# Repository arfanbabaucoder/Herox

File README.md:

# HeroX

HeroX is my custom full-size mechanical keyboard project, built around a **Seeed Studio XIAO nRF52840**.

so basically i wanted a full-size board that could do Bluetooth and normal USB, but i also wanted to go further than just switches on a PCB.. per-key RGB, haptics, a media knob, battery tracking, multiple Bluetooth profiles, a proper 4-layer board and a custom case. i designed the electronics in KiCad, worked on the case in Fusion 360 and put together the firmware side too, which turned into a much bigger rabbit hole than expected lol

## why i made this

i wanted a keyboard that i could actually use as a daily driver without giving up the full-size layout, numpad, navigation cluster or function row, but i didnt want it to be just another giant boring rectangle either

main goals :

- design a full-size keyboard PCB in KiCad
- support Bluetooth and wired USB-C
- scan the keyboard matrix using I2C GPIO expanders so the small XIAO controller has enough pins
- add addressable SK6812 MINI-E RGB lighting
- include a media encoder, haptic feedback and battery monitoring
- make a proper 4-layer PCB intended for manufacturing
- design a custom case in Fusion 360
- keep the project files, production references, images and BOM together so the build is reproducible

the fun part is that everything affects everything else.. a small PCB change can affect case clearances, connector access and firmware pin assignments. thats the kind of detail that makes a custom keyboard project way more involved than it looks from the top

## project status

HeroX is documented here as a design project with CAD, PCB screenshots, firmware-related screenshots and a parts list. the hardware still needs to be assembled and tested before i can claim that every feature works on a finished physical board, so treat this as a design/build project rather than a fully validated retail product

whats in this repo :

- `3D CAD/` — exported 3D model files
- `BOM Images/` — supplier and component sourcing screenshots
- `Firmware/` — firmware-related project files
- `Fusion/` — Fusion 360 design files
- `Images/` — PCB, schematic, CAD and firmware screenshots
- `PCB/` — KiCad PCB design files
- `PDFs/` — exported project documents, if present
- `Production/` — manufacturing outputs, if present
- `BOM.csv` — parts list, supplier links and estimated prices

## hardware summary

| | |
|---|---|
| Project | HeroX |
| Layout | Full-size mechanical keyboard |
| Controller | Seeed Studio XIAO nRF52840 |
| Connectivity target | Bluetooth LE and wired USB-C |
| Matrix support | I2C GPIO expanders (PCA9555-compatible parts listed in BOM) |
| Switch diodes | 1N4148W SOD-123 |
| RGB | SK6812 MINI-E addressable LEDs |
| Battery monitoring | MAX17048 fuel-gauge IC listed in BOM |
| Haptics | DRV2605L haptic-driver IC listed in BOM |
| Controls | Rotary/media encoder shown in the project design |
| Switches | Akko V3 Creamy Blue Pro 5-pin MX switches |
| Keycaps | 104/108-key ANSI PBT set |
| Stabilizers | DUROCK V3 100% PCB-mount kit |
| PCB | 4-layer board quote listed in the BOM |
| CAD | Fusion 360 and exported 3D files |

some of the interesting engineering is hidden underneath the keycaps.. the PCB has to fit the whole matrix, lighting and support circuits, while the case needs to line up with the switches, ports and controls. the CAD and PCB images below show the project from a few different angles

## images

### PCB and switch layout

### PCB routing and board layers

### schematic

the schematic screenshots show the keyboard matrix and the supporting circuits used across the design

### firmware and build screenshots

### CAD and case

## repo file checklist

the folder names in the current project are:

- `PCB/` — KiCad design files
- `3D CAD/` — 3D exports
- `Fusion/` — editable Fusion design files
- `Firmware/` — firmware files
- `Production/` — manufacturing outputs
- `PDFs/` — PDF exports
- `Images/` — project screenshots used in this README
- `BOM Images/` — sourcing screenshots
- `BOM.csv` — complete bill of materials

the exact filenames inside each folder may change as the project gets updated, so open the folders to find the latest versions. this README intentionally uses the visible folder structure rather than guessing filenames that may not exist in the repository

## cad

the case was designed in Fusion 360. the `Fusion/` folder is intended for the editable design, while `3D CAD/` contains exported geometry for viewing, modifying or preparing for printing. check the available formats in those folders before starting a print or manufacturing order

the case and PCB need to be checked together before fabrication: switch alignment, board mounting, connector access and clearance around the controls all matter. use the supplied CAD and PCB files as the source of truth for the current revision

## firmware note

the project includes a `Firmware/` folder and firmware/build screenshots. the controller listed in the BOM is the Seeed Studio XIAO nRF52840, and the design includes components associated with wireless operation, RGB, battery monitoring and haptic feedback

firmware features and flashing steps should be confirmed against the actual files in `Firmware/` before building. i dont want to claim a particular key combination, flashing image or feature is ready until it has been checked against the committed firmware revision

## bom

the full bill of materials is in [`BOM.csv`](BOM.csv). it includes the part description, quantity, supplier, supplier link and listed price in rupees. supplier prices and stock can change, and some quantities reflect supplier pack sizes or minimum order quantities rather than the exact number installed on the keyboard

**listed BOM total: ₹36,382.32**

a few notable parts from the BOM:

| Part | Purpose |
|---|---|
| Seeed Studio XIAO nRF52840 | Main controller |
| PCA9555DWR I/O expanders | Expand available GPIO for the keyboard matrix |
| 1N4148W SOD-123 diodes | Per-switch matrix diodes |
| SK6812 MINI-E | Addressable RGB lighting |
| MAX17048 fuel gauge | Battery monitoring |
| DRV2605L | Haptic driver |
| Akko V3 Creamy Blue Pro switches | Mechanical key switches |
| DUROCK V3 stabilizer kit | Stabilization for larger keys |
| 104/108-key ANSI PBT set | Keycaps |
| 4-layer PCB | Main keyboard circuit board |

prices are the values currently captured in the BOM, not a guaranteed final build cost. the total can change with shipping, taxes, revised quotes, spare parts and supplier minimums. check the links in `BOM.csv` before ordering anything

## build notes

- inspect the PCB and schematic before ordering a board
- verify the exact component substitutions and footprints against the BOM and KiCad files
- check the CAD exports against the current PCB revision before printing the case
- use a suitable protected battery and verify polarity and connector wiring before connecting it
- test the board in stages instead of powering every subsystem at once
- confirm firmware configuration and flashing instructions from the files in `Firmware/`

## contributing / questions

this is a personal custom keyboard project, and im sharing the design files and build notes so the work is easier to understand and build on. if you spot an issue or have a suggestion, feel free to open an issue on GitHub

thanks for checking out HeroX.. this project is a mix of PCB design, CAD, sourcing and embedded work, and its been a pretty great way to learn how all those pieces fit together :)

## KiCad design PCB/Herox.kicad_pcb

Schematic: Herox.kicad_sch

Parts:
A1: Seeeduino XIAO nRF52840; Xiao_nRF52840_ACH
C1: 100n U1; C_0603_1608Metric
C2: 100n U2; C_0603_1608Metric
C3: 10u BAT; C_0805_2012Metric
C4: 10u MCU; C_0805_2012Metric
C5: 47u RGB; C_0805_2012Metric
C6: 1u DRV REG; C_0603_1608Metric
C7: 100nF X7R; C_0603_1608Metric
D1, D2, D3, D4, D5, D6, D7, D8, D9, D10, D11, D12, D13, D14, D15, D16, D17, D18, D19, D20, D21, D22, D23, D24, D25, D26, D27, D28, D29, D30, D31, D32, D33, D34, D35, D36, D37, D38, D39, D40, D41, D42, D43, D44, D45, D46, D47, D48, D49, D50, D51, D52, D53, D54, D55, D56, D57, D58, D59, D60, D61, D62, D63, D64, D65, D66, D67, D68, D69, D70, D71, D72, D73, D74, D75, D76, D77, D78, D79, D80, D81, D82, D83, D84, D85, D86, D87, D88, D89, D90, D91, D92, D93, D94, D95, D96, D97, D98, D99, D100, D101, D102, D103, D104: 1N4148W; D_SOD-123
ENC1: MEDIA ENCODER; RotaryEncoder_Alps_EC11E-Switch_Vertical_H20mm
F1: PTC 1.1A; Fuse_1206_3216Metric
F2: PTC 0.5A / USB RGB; Fuse_1206_3216Metric; Manufacturer Part Number 0ZCJ0050FF2G
J1: PROTECTED Li-Po 3.7V; JST_PH_S2B-PH-K_1x02_P2.00mm_Horizontal
J2: LRA ACTUATOR; JST_PH_S2B-PH-K_1x02_P2.00mm_Horizontal
J3: LOW-POWER DISPLAY; PinHeader_1x06_P2.54mm_Vertical
J4: AMBIENT SENSOR / EXPANSION; PinHeader_1x06_P2.54mm_Vertical
J5: SWD DEBUG; PinHeader_1x04_P2.54mm_Vertical
LED1, LED2, LED3, LED4, LED5, LED6, LED7, LED8, LED9, LED10, LED11, LED12, LED13, LED14, LED15, LED16, LED17, LED18, LED19, LED20, LED21, LED22, LED23, LED24, LED25, LED26, LED27, LED28, LED29, LED30, LED31, LED32, LED33, LED34, LED35, LED36, LED37, LED38, LED39, LED40, LED41, LED42, LED43, LED44, LED45, LED46, LED47, LED48, LED49, LED50, LED51, LED52, LED53, LED54, LED55, LED56, LED57, LED58, LED59, LED60, LED61, LED62, LED63, LED64, LED65, LED66, LED67, LED68, LED69, LED70, LED71, LED72, LED73, LED74, LED75, LED76, LED77, LED78, LED79, LED80, LED81, LED82, LED83, LED84, LED85, LED86, LED87, LED88, LED89, LED90, LED91, LED92, LED93, LED94, LED95, LED96, LED97, LED98, LED99, LED100, LED101, LED102, LED103, LED104: SK6812MINI-E; LED_SK6812MINI-E_3.2x2.8mm_P1.5mm_ReverseMount
LED105, LED106: XL-1608UGC-04 GREEN; LED_0603_1608Metric
LED107, LED108, LED109: LTST-C193TBKT-5A BLUE; LED_0603_1608Metric
R1: 4.7k SDA; R_0603_1608Metric
R2: 4.7k SCL; R_0603_1608Metric
R3: 10k INT; R_0603_1608Metric
R4, R5, R6, R7, R8: 1k STATUS; R_0603_1608Metric
R12: 33R; R_0603_1608Metric
SW1: Esc; SW_MX_1.00u
SW2: F1; SW_MX_1.00u
SW3: F2; SW_MX_1.00u
SW4: F3; SW_MX_1.00u
SW5: F4; SW_MX_1.00u
SW6: F5; SW_MX_1.00u
SW7: F6; SW_MX_1.00u
SW8: F7; SW_MX_1.00u
SW9: F8; SW_MX_1.00u
SW10: F9; SW_MX_1.00u
SW11: F10; SW_MX_1.00u
SW12: F11; SW_MX_1.00u
SW13: F12; SW_MX_1.00u
SW14: PrtSc; SW_MX_1.00u
SW15: Scroll; SW_MX_1.00u
SW16: Pause; SW_MX_1.00u
SW17: `~; SW_MX_1.00u
SW18: 1!; SW_MX_1.00u
SW19: 2@; SW_MX_1.00u
SW20: 3#; SW_MX_1.00u
SW21: 4$; SW_MX_1.00u
SW22: 5%; SW_MX_1.00u
SW23: 6^; SW_MX_1.00u
SW24: 7&; SW_MX_1.00u
SW25: 8*; SW_MX_1.00u
SW26: 9(; SW_MX_1.00u
SW27: 0); SW_MX_1.00u
SW28: -_; SW_MX_1.00u
SW29: =+; SW_MX_1.00u
SW30: Backspace; SW_MX_2.00u
SW31: Insert; SW_MX_1.00u
SW32: Home; SW_MX_1.00u
SW33: PgUp; SW_MX_1.00u
SW34: Num; SW_MX_1.00u
SW35: /; SW_MX_1.00u
SW36: *; SW_MX_1.00u
SW37: -; SW_MX_1.00u
SW38: Tab; SW_MX_1.50u
SW39: Q; SW_MX_1.00u
SW40: W; SW_MX_1.00u
SW41: E; SW_MX_1.00u
SW42: R; SW_MX_1.00u
SW43: T; SW_MX_1.00u
SW44: Y; SW_MX_1.00u
SW45: U; SW_MX_1.00u
SW46: I; SW_MX_1.00u
SW47: O; SW_MX_1.00u
SW48: P; SW_MX_1.00u
SW49: [{; SW_MX_1.00u
SW50: ]}; SW_MX_1.00u
SW51: \|; SW_MX_1.50u
SW52: Delete; SW_MX_1.00u
SW53: End; SW_MX_1.00u
SW54: PgDn; SW_MX_1.00u
SW55: 7; SW_MX_1.00u
SW56: 8; SW_MX_1.00u
SW57: 9; SW_MX_1.00u
SW58: +; SW_MX_2.00u_Vertical
SW59: Caps; SW_MX_1.75u
SW60: A; SW_MX_1.00u
SW61: S; SW_MX_1.00u
SW62: D; SW_MX_1.00u
SW63: F; SW_MX_1.00u
SW64: G; SW_MX_1.00u
SW65: H; SW_MX_1.00u
SW66: J; SW_MX_1.00u
SW67: K; SW_MX_1.00u
SW68: L; SW_MX_1.00u
SW69: ;:; SW_MX_1.00u
SW70: '"; SW_MX_1.00u
SW71: Enter; SW_MX_2.25u
SW72: 4; SW_MX_1.00u
SW73: 5; SW_MX_1.00u
SW74: 6; SW_MX_1.00u
SW75: LShift; SW_MX_2.25u
SW76: Z; SW_MX_1.00u
SW77: X; SW_MX_1.00u
SW78: C; SW_MX_1.00u
SW79: V; SW_MX_1.00u
SW80: B; SW_MX_1.00u
SW81: N; SW_MX_1.00u
SW82: M; SW_MX_1.00u
SW83: ,<; SW_MX_1.00u
SW84: .>; SW_MX_1.00u
SW85: /?; SW_MX_1.00u
SW86: RShift; SW_MX_2.75u
SW87: Up; SW_MX_1.00u
SW88: 1; SW_MX_1.00u
SW89: 2; SW_MX_1.00u
SW90: 3; SW_MX_1.00u
SW91: NEnter; SW_MX_2.00u_Vertical
SW92: LCtrl; SW_MX_1.25u
SW93: LWin; SW_MX_1.25u
SW94: LAlt; SW_MX_1.25u
SW95: Space; SW_MX_6.25u
SW96: RAlt; SW_MX_1.25u
SW97: RWin; SW_MX_1.25u
SW98: Menu; SW_MX_1.25u
SW99: RCtrl; SW_MX_1.25u
SW100: Left; SW_MX_1.00u
SW101: Down; SW_MX_1.00u
SW102: Right; SW_MX_1.00u
SW103: 0; SW_MX_2.00u
SW104: .; SW_MX_1.00u
SWP1: HARD POWER; SW_SPDT_CK_JS102011SAQN
U1: TCA9555DW / ROW DRIVE; SOIC-24W_7.5x15.4mm_P1.27mm
U2: TCA9555DW / COLUMN SENSE; SOIC-24W_7.5x15.4mm_P1.27mm
U3: MAX17048G+T10 FUEL GAUGE; TDFN-8-1EP_2x2mm_P0.5mm_EP0.8x1.2mm
U4: DRV2605L HAPTIC DRIVER; MSOP-10_3x3mm_P0.5mm
U5: 74LVC1G125GW,125; SOT-353_SC-70-5; Manufacturer Part Number 74LVC1G125GW,125

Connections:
/+3V3: A1.10 (3V3), C1.1, C2.1, C4.1, J3.2, J4.2, J5.2, R1.1, R2.1, R3.1, R4.1, R5.1, R6.1, R7.1, R8.1, U1.24 (VCC), U2.21 (A0), U2.24 (VCC), U4.5 (EN), U4.6 (VDD/NC), U4.10 (VDD)
/+5V_RGB: C5.1, C7.1, F2.2, LED1.3 (VDD), LED2.3 (VDD), LED3.3 (VDD), LED4.3 (VDD), LED5.3 (VDD), LED6.3 (VDD), LED7.3 (VDD), LED8.3 (VDD), LED9.3 (VDD), LED10.3 (VDD), LED11.3 (VDD), LED12.3 (VDD), LED13.3 (VDD), LED14.3 (VDD), LED15.3 (VDD), LED16.3 (VDD), LED17.3 (VDD), LED18.3 (VDD), LED19.3 (VDD), LED20.3 (VDD), LED21.3 (VDD), LED22.3 (VDD), LED23.3 (VDD), LED24.3 (VDD), LED25.3 (VDD), LED26.3 (VDD), LED27.3 (VDD), LED28.3 (VDD), LED29.3 (VDD), LED30.3 (VDD), LED31.3 (VDD), LED32.3 (VDD), LED33.3 (VDD), LED34.3 (VDD), LED35.3 (VDD), LED36.3 (VDD), LED37.3 (VDD), LED38.3 (VDD), LED39.3 (VDD), LED40.3 (VDD), LED41.3 (VDD), LED42.3 (VDD), LED43.3 (VDD), LED44.3 (VDD), LED45.3 (VDD), LED46.3 (VDD), LED47.3 (VDD), LED48.3 (VDD), LED49.3 (VDD), LED50.3 (VDD), LED51.3 (VDD), LED52.3 (VDD), LED53.3 (VDD), LED54.3 (VDD), LED55.3 (VDD), LED56.3 (VDD), LED57.3 (VDD), LED58.3 (VDD), LED59.3 (VDD), LED60.3 (VDD), LED61.3 (VDD), LED62.3 (VDD), LED63.3 (VDD), LED64.3 (VDD), LED65.3 (VDD), LED66.3 (VDD), LED67.3 (VDD), LED68.3 (VDD), LED69.3 (VDD), LED70.3 (VDD), LED71.3 (VDD), LED72.3 (VDD), LED73.3 (VDD), LED74.3 (VDD), LED75.3 (VDD), LED76.3 (VDD), LED77.3 (VDD), LED78.3 (VDD), LED79.3 (VDD), LED80.3 (VDD), LED81.3 (VDD), LED82.3 (VDD), LED83.3 (VDD), LED84.3 (VDD), LED85.3 (VDD), LED86.3 (VDD), LED87.3 (VDD), LED88.3 (VDD), LED89.3 (VDD), LED90.3 (VDD), LED91.3 (VDD), LED92.3 (VDD), LED93.3 (VDD), LED94.3 (VDD), LED95.3 (VDD), LED96.3 (VDD), LED97.3 (VDD), LED98.3 (VDD), LED99.3 (VDD), LED100.3 (VDD), LED101.3 (VDD), LED102.3 (VDD), LED103.3 (VDD), LED104.3 (VDD), U5.5 (VCC)
/COL0: SW1.1, SW14.1, SW27.1, SW40.1, SW53.1, SW66.1, SW79.1, SW92.1, U2.4 (P00)
/COL1: SW2.1, SW15.1, SW28.1, SW41.1, SW54.1, SW67.1, SW80.1, SW93.1, U2.5 (P01)
/COL2: SW3.1, SW16.1, SW29.1, SW42.1, SW55.1, SW68.1, SW81.1, SW94.1, U2.6 (P02)
/COL3: SW4.1, SW17.1, SW30.1, SW43.1, SW56.1, SW69.1, SW82.1, SW95.1, U2.7 (P03)
/COL4: SW5.1, SW18.1, SW31.1, SW44.1, SW57.1, SW70.1, SW83.1, SW96.1, U2.8 (P04)
/COL5: SW6.1, SW19.1, SW32.1, SW45.1, SW58.1, SW71.1, SW84.1, SW97.1, U2.9 (P05)
/COL6: SW7.1, SW20.1, SW33.1, SW46.1, SW59.1, SW72.1, SW85.1, SW98.1, U2.10 (P06)
/COL7: SW8.1, SW21.1, SW34.1, SW47.1, SW60.1, SW73.1, SW86.1, SW99.1, U2.11 (P07)
/COL8: SW9.1, SW22.1, SW35.1, SW48.1, SW61.1, SW74.1, SW87.1, SW100.1, U2.13 (P10)
/COL9: SW10.1, SW23.1, SW36.1, SW49.1, SW62.1, SW75.1, SW88.1, SW101.1, U2.14 (P11)
/COL10: SW11.1, SW24.1, SW37.1, SW50.1, SW63.1, SW76.1, SW89.1, SW102.1, U2.15 (P12)
/COL11: SW12.1, SW25.1, SW38.1, SW51.1, SW64.1, SW77.1, SW90.1, SW103.1, U2.16 (P13)
/COL12: SW13.1, SW26.1, SW39.1, SW52.1, SW65.1, SW78.1, SW91.1, SW104.1, U2.17 (P14)
/DISP_INT: A1.11 (P1.15), J3.5
/DRV_REG: C6.1, U4.1 (REG)
/ENC_A: A1.3 (P0.28), ENC1.A
/ENC_B: A1.4 (P0.29), ENC1.C
/ENC_SW: A1.7 (P1.11), ENC1.S1
/EX_INT: A1.2 (P0.03), J4.5, R3.2, U1.1 (~INT), U2.1 (~INT)
/FUEL_INT: A1.12 (P1.14), U3.5
/GND: A1.9 (GND), A1.15 (BAT-), A1.22 (GND), C1.2, C2.2, C3.2, C4.2, C5.2, C6.2, C7.2, ENC1.B, ENC1.S2, J1.2, J3.1, J4.1, J5.1, LED1.1 (VSS), LED2.1 (VSS), LED3.1 (VSS), LED4.1 (VSS), LED5.1 (VSS), LED6.1 (VSS), LED7.1 (VSS), LED8.1 (VSS), LED9.1 (VSS), LED10.1 (VSS), LED11.1 (VSS), LED12.1 (VSS), LED13.1 (VSS), LED14.1 (VSS), LED15.1 (VSS), LED16.1 (VSS), LED17.1 (VSS), LED18.1 (VSS), LED19.1 (VSS), LED20.1 (VSS), LED21.1 (VSS), LED22.1 (VSS), LED23.1 (VSS), LED24.1 (VSS), LED25.1 (VSS), LED26.1 (VSS), LED27.1 (VSS), LED28.1 (VSS), LED29.1 (VSS), LED30.1 (VSS), LED31.1 (VSS), LED32.1 (VSS), LED33.1 (VSS), LED34.1 (VSS), LED35.1 (VSS), LED36.1 (VSS), LED37.1 (VSS), LED38.1 (VSS), LED39.1 (VSS), LED40.1 (VSS), LED41.1 (VSS), LED42.1 (VSS), LED43.1 (VSS), LED44.1 (VSS), LED45.1 (VSS), LED46.1 (VSS), LED47.1 (VSS), LED48.1 (VSS), LED49.1 (VSS), LED50.1 (VSS), LED51.1 (VSS), LED52.1 (VSS), LED53.1 (VSS), LED54.1 (VSS), LED55.1 (VSS), LED56.1 (VSS), LED57.1 (VSS), LED58.1 (VSS), LED59.1 (VSS), LED60.1 (VSS), LED61.1 (VSS), LED62.1 (VSS), LED63.1 (VSS), LED64.1 (VSS), LED65.1 (VSS), LED66.1 (VSS), LED67.1 (VSS), LED68.1 (VSS), LED69.1 (VSS), LED70.1 (VSS), LED71.1 (VSS), LED72.1 (VSS), LED73.1 (VSS), LED74.1 (VSS), LED75.1 (VSS), LED76.1 (VSS), LED77.1 (VSS), LED78.1 (VSS), LED79.1 (VSS), LED80.1 (VSS), LED81.1 (VSS), LED82.1 (VSS), LED83.1 (VSS), LED84.1 (VSS), LED85.1 (VSS), LED86.1 (VSS), LED87.1 (VSS), LED88.1 (VSS), LED89.1 (VSS), LED90.1 (VSS), LED91.1 (VSS), LED92.1 (VSS), LED93.1 (VSS), LED94.1 (VSS), LED95.1 (VSS), LED96.1 (VSS), LED97.1 (VSS), LED98.1 (VSS), LED99.1 (VSS), LED100.1 (VSS), LED101.1 (VSS), LED102.1 (VSS), LED103.1 (VSS), LED104.1 (VSS), U1.2 (A1), U1.3 (A2), U1.12 (GND), U1.21 (A0), U2.2 (A1), U2.3 (A2), U2.12 (GND), U3.3, U3.4, U3.9, U4.4 (IN/TRIG), U4.8 (GND), U5.1, U5.3 (GND)
/HAPTIC_N: J2.2, U4.9 (OUT-)
/HAPTIC_P: J2.1, U4.7 (OUT+)
/I2C_SCL: A1.6 (P0.05), J3.4, J4.4, R2.2, U1.22 (SCL), U2.22 (SCL), U3.7, U4.2 (SCL)
/I2C_SDA: A1.5 (P0.04), J3.3, J4.3, J5.3, R1.2, U1.23 (SDA), U2.23 (SDA), U3.6, U4.3 (SDA)
/IND_BLE1_N: LED107.1 (K), U1.15 (P12)
/IND_BLE2_N: LED108.1 (K), U1.16 (P13)
/IND_BLE3_N: LED109.1 (K), U1.17 (P14)
/IND_CAPS_N: LED105.1 (K), U1.13 (P10)
/IND_NUM_N: LED106.1 (K), U1.14 (P11)
/KSW1: D1.2 (A), SW1.2
/KSW2: D2.2 (A), SW2.2
/KSW3: D3.2 (A), SW3.2
/KSW4: D4.2 (A), SW4.2
/KSW5: D5.2 (A), SW5.2
/KSW6: D6.2 (A), SW6.2
/KSW7: D7.2 (A), SW7.2
/KSW8: D8.2 (A), SW8.2
/KSW9: D9.2 (A), SW9.2
/KSW10: D10.2 (A), SW10.2
/KSW11: D11.2 (A), SW11.2
/KSW12: D12.2 (A), SW12.2
/KSW13: D13.2 (A), SW13.2
/KSW14: D14.2 (A), SW14.2
/KSW15: D15.2 (A), SW15.2
/KSW16: D16.2 (A), SW16.2
/KSW17: D17.2 (A), SW17.2
/KSW18: D18.2 (A), SW18.2
/KSW19: D19.2 (A), SW19.2
/KSW20: D20.2 (A), SW20.2
/KSW21: D21.2 (A), SW21.2
/KSW22: D22.2 (A), SW22.2
/KSW23: D23.2 (A), SW23.2
/KSW24: D24.2 (A), SW24.2
/KSW25: D25.2 (A), SW25.2
/KSW26: D26.2 (A), SW26.2
/KSW27: D27.2 (A), SW27.2
/KSW28: D28.2 (A), SW28.2
/KSW29: D29.2 (A), SW29.2
/KSW30: D30.2 (A), SW30.2
/KSW31: D31.2 (A), SW31.2
/KSW32: D32.2 (A), SW32.2
/KSW33: D33.2 (A), SW33.2
/KSW34: D34.2 (A), SW34.2
/KSW35: D35.2 (A), SW35.2
/KSW36: D36.2 (A), SW36.2
/KSW37: D37.2 (A), SW37.2
/KSW38: D38.2 (A), SW38.2
/KSW39: D39.2 (A), SW39.2
/KSW40: D40.2 (A), SW40.2
/KSW41: D41.2 (A), SW41.2
/KSW42: D42.2 (A), SW42.2
/KSW43: D43.2 (A), SW43.2
/KSW44: D44.2 (A), SW44.2
/KSW45: D45.2 (A), SW45.2
/KSW46: D46.2 (A), SW46.2
/KSW47: D47.2 (A), SW47.2
/KSW48: D48.2 (A), SW48.2
/KSW49: D49.2 (A), SW49.2
/KSW50: D50.2 (A), SW50.2
/KSW51: D51.2 (A), SW51.2
/KSW52: D52.2 (A), SW52.2
/KSW53: D53.2 (A), SW53.2
/KSW54: D54.2 (A), SW54.2
/KSW55: D55.2 (A), SW55.2
/KSW56: D56.2 (A), SW56.2
/KSW57: D57.2 (A), SW57.2
/KSW58: D58.2 (A), SW58.2
/KSW59: D59.2 (A), SW59.2
/KSW60: D60.2 (A), SW60.2
/KSW61: D61.2 (A), SW61.2
/KSW62: D62.2 (A), SW62.2
/KSW63: D63.2 (A), SW63.2
/KSW64: D64.2 (A), SW64.2
/KSW65: D65.2 (A), SW65.2
/KSW66: D66.2 (A), SW66.2
/KSW67: D67.2 (A), SW67.2
/KSW68: D68.2 (A), SW68.2
/KSW69: D69.2 (A), SW69.2
/KSW70: D70.2 (A), SW70.2
/KSW71: D71.2 (A), SW71.2
/KSW72: D72.2 (A), SW72.2
/KSW73: D73.2 (A), SW73.2
/KSW74: D74.2 (A), SW74.2
/KSW75: D75.2 (A), SW75.2
/KSW76: D76.2 (A), SW76.2
/KSW77: D77.2 (A), SW77.2
/KSW78: D78.2 (A), SW78.2
/KSW79: D79.2 (A), SW79.2
/KSW80: D80.2 (A), SW80.2
/KSW81: D81.2 (A), SW81.2
/KSW82: D82.2 (A), SW82.2
/KSW83: D83.2 (A), SW83.2
/KSW84: D84.2 (A), SW84.2
/KSW85: D85.2 (A), SW85.2
/KSW86: D86.2 (A), SW86.2
/KSW87: D87.2 (A), SW87.2
/KSW88: D88.2 (A), SW88.2
/KSW89: D89.2 (A), SW89.2
/KSW90: D90.2 (A), SW90.2
/KSW91: D91.2 (A), SW91.2
/KSW92: D92.2 (A), SW92.2
/KSW93: D93.2 (A), SW93.2
/KSW94: D94.2 (A), SW94.2
/KSW95: D95.2 (A), SW95.2
/KSW96: D96.2 (A), SW96.2
/KSW97: D97.2 (A), SW97.2
/KSW98: D98.2 (A), SW98.2
/KSW99: D99.2 (A), SW99.2
/KSW100: D100.2 (A), SW100.2
/KSW101: D101.2 (A), SW101.2
/KSW102: D102.2 (A), SW102.2
/KSW103: D103.2 (A), SW103.2
/KSW104: D104.2 (A), SW104.2
/NRST: A1.21 (RST), J3.6, J5.4
/RGB_1: LED1.4 (DOUT), LED2.2 (DIN)
/RGB_2: LED2.4 (DOUT), LED3.2 (DIN)
/RGB_3: LED3.4 (DOUT), LED4.2 (DIN)
/RGB_4: LED4.4 (DOUT), LED5.2 (DIN)
/RGB_5: LED5.4 (DOUT), LED6.2 (DIN)
/RGB_6: LED6.4 (DOUT), LED7.2 (DIN)
/RGB_7: LED7.4 (DOUT), LED8.2 (DIN)
/RGB_8: LED8.4 (DOUT), LED9.2 (DIN)
/RGB_9: LED9.4 (DOUT), LED10.2 (DIN)
/RGB_10: LED10.4 (DOUT), LED11.2 (DIN)
/RGB_11: LED11.4 (DOUT), LED12.2 (DIN)
/RGB_12: LED12.4 (DOUT), LED13.2 (DIN)
/RGB_13: LED13.4 (DOUT), LED14.2 (DIN)
/RGB_14: LED14.4 (DOUT), LED15.2 (DIN)
/RGB_15: LED15.4 (DOUT), LED16.2 (DIN)
/RGB_16: LED16.4 (DOUT), LED17.2 (DIN)
/RGB_17: LED17.4 (DOUT), LED18.2 (DIN)
/RGB_18: LED18.4 (DOUT), LED19.2 (DIN)
/RGB_19: LED19.4 (DOUT), LED20.2 (DIN)
/RGB_20: LED20.4 (DOUT), LED21.2 (DIN)
/RGB_21: LED21.4 (DOUT), LED22.2 (DIN)
/RGB_22: LED22.4 (DOUT), LED23.2 (DIN)
/RGB_23: LED23.4 (DOUT), LED24.2 (DIN)
/RGB_24: LED24.4 (DOUT), LED25.2 (DIN)
/RGB_25: LED25.4 (DOUT), LED26.2 (DIN)
/RGB_26: LED26.4 (DOUT), LED27.2 (DIN)
/RGB_27: LED27.4 (DOUT), LED28.2 (DIN)
/RGB_28: LED28.4 (DOUT), LED29.2 (DIN)
/RGB_29: LED29.4 (DOUT), LED30.2 (DIN)
/RGB_30: LED30.4 (DOUT), LED31.2 (DIN)
/RGB_31: LED31.4 (DOUT), LED32.2 (DIN)
/RGB_32: LED32.4 (DOUT), LED33.2 (DIN)
/RGB_33: LED33.4 (DOUT), LED34.2 (DIN)
/RGB_34: LED34.4 (DOUT), LED35.2 (DIN)
/RGB_35: LED35.4 (DOUT), LED36.2 (DIN)
/RGB_36: LED36.4 (DOUT), LED37.2 (DIN)
/RGB_37: LED37.4 (DOUT), LED38.2 (DIN)
/RGB_38: LED38.4 (DOUT), LED39.2 (DIN)
/RGB_39: LED39.4 (DOUT), LED40.2 (DIN)
/RGB_40: LED40.4 (DOUT), LED41.2 (DIN)
/RGB_41: LED41.4 (DOUT), LED42.2 (DIN)
/RGB_42: LED42.4 (DOUT), LED43.2 (DIN)
/RGB_43: LED43.4 (DOUT), LED44.2 (DIN)
/RGB_44: LED44.4 (DOUT), LED45.2 (DIN)
/RGB_45: LED45.4 (DOUT), LED46.2 (DIN)
/RGB_46: LED46.4 (DOUT), LED47.2 (DIN)
/RGB_47: LED47.4 (DOUT), LED48.2 (DIN)
/RGB_48: LED48.4 (DOUT), LED49.2 (DIN)
/RGB_49: LED49.4 (DOUT), LED50.2 (DIN)
/RGB_50: LED50.4 (DOUT), LED51.2 (DIN)
/RGB_51: LED51.4 (DOUT), LED52.2 (DIN)
/RGB_52: LED52.4 (DOUT), LED53.2 (DIN)
/RGB_53: LED53.4 (DOUT), LED54.2 (DIN)
/RGB_54: LED54.4 (DOUT), LED55.2 (DIN)
/RGB_55: LED55.4 (DOUT), LED56.2 (DIN)
/RGB_56: LED56.4 (DOUT), LED57.2 (DIN)
/RGB_57: LED57.4 (DOUT), LED58.2 (DIN)
/RGB_58: LED58.4 (DOUT), LED59.2 (DIN)
/RGB_59: LED59.4 (DOUT), LED60.2 (DIN)
/RGB_60: LED60.4 (DOUT), LED61.2 (DIN)
/RGB_61: LED61.4 (DOUT), LED62.2 (DIN)
/RGB_62: LED62.4 (DOUT), LED63.2 (DIN)
/RGB_63: LED63.4 (DOUT), LED64.2 (DIN)
/RGB_64: LED64.4 (DOUT), LED65.2 (DIN)
/RGB_65: LED65.4 (DOUT), LED66.2 (DIN)
/RGB_66: LED66.4 (DOUT), LED67.2 (DIN)
/RGB_67: LED67.4 (DOUT), LED68.2 (DIN)
/RGB_68: LED68.4 (DOUT), LED69.2 (DIN)
/RGB_69: LED69.4 (DOUT), LED70.2 (DIN)
/RGB_70: LED70.4 (DOUT), LED71.2 (DIN)
/RGB_71: LED71.4 (DOUT), LED72.2 (DIN)
/RGB_72: LED72.4 (DOUT), LED73.2 (DIN)
/RGB_73: LED73.4 (DOUT), LED74.2 (DIN)
/RGB_74: LED74.4 (DOUT), LED75.2 (DIN)
/RGB_75: LED75.4 (DOUT), LED76.2 (DIN)
/RGB_76: LED76.4 (DOUT), LED77.2 (DIN)
/RGB_77: LED77.4 (DOUT), LED78.2 (DIN)
/RGB_78: LED78.4 (DOUT), LED79.2 (DIN)
/RGB_79: LED79.4 (DOUT), LED80.2 (DIN)
/RGB_80: LED80.4 (DOUT), LED81.2 (DIN)
/RGB_81: LED81.4 (DOUT), LED82.2 (DIN)
/RGB_82: LED82.4 (DOUT), LED83.2 (DIN)
/RGB_83: LED83.4 (DOUT), LED84.2 (DIN)
/RGB_84: LED84.4 (DOUT), LED85.2 (DIN)
/RGB_85: LED85.4 (DOUT), LED86.2 (DIN)
/RGB_86: LED86.4 (DOUT), LED87.2 (DIN)
/RGB_87: LED87.4 (DOUT), LED88.2 (DIN)
/RGB_88: LED88.4 (DOUT), LED89.2 (DIN)
/RGB_89: LED89.4 (DOUT), LED90.2 (DIN)
/RGB_90: LED90.4 (DOUT), LED91.2 (DIN)
/RGB_91: LED91.4 (DOUT), LED92.2 (DIN)
/RGB_92: LED92.4 (DOUT), LED93.2 (DIN)
/RGB_93: LED93.4 (DOUT), LED94.2 (DIN)
/RGB_94: LED94.4 (DOUT), LED95.2 (DIN)
/RGB_95: LED95.4 (DOUT), LED96.2 (DIN)
/RGB_96: LED96.4 (DOUT), LED97.2 (DIN)
/RGB_97: LED97.4 (DOUT), LED98.2 (DIN)
/RGB_98: LED98.4 (DOUT), LED99.2 (DIN)
/RGB_99: LED99.4 (DOUT), LED100.2 (DIN)
/RGB_100: LED100.4 (DOUT), LED101.2 (DIN)
/RGB_101: LED101.4 (DOUT), LED102.2 (DIN)
/RGB_102: LED102.4 (DOUT), LED103.2 (DIN)
/RGB_103: LED103.4 (DOUT), LED104.2 (DIN)
/RGB_DATA: LED1.2 (DIN), R12.2
/RGB_DATA_3V3: A1.1 (P0.02), U5.2
/ROW0: D1.1 (K), D2.1 (K), D3.1 (K), D4.1 (K), D5.1 (K), D6.1 (K), D7.1 (K), D8.1 (K), D9.1 (K), D10.1 (K), D11.1 (K), D12.1 (K), D13.1 (K), U1.4 (P00)
/ROW1: D14.1 (K), D15.1 (K), D16.1 (K), D17.1 (K), D18.1 (K), D19.1 (K), D20.1 (K), D21.1 (K), D22.1 (K), D23.1 (K), D24.1 (K), D25.1 (K), D26.1 (K), U1.5 (P01)
/ROW2: D27.1 (K), D28.1 (K), D29.1 (K), D30.1 (K), D31.1 (K), D32.1 (K), D33.1 (K), D34.1 (K), D35.1 (K), D36.1 (K), D37.1 (K), D38.1 (K), D39.1 (K), U1.6 (P02)
/ROW3: D40.1 (K), D41.1 (K), D42.1 (K), D43.1 (K), D44.1 (K), D45.1 (K), D46.1 (K), D47.1 (K), D48.1 (K), D49.1 (K), D50.1 (K), D51.1 (K), D52.1 (K), U1.7 (P03)
/ROW4: D53.1 (K), D54.1 (K), D55.1 (K), D56.1 (K), D57.1 (K), D58.1 (K), D59.1 (K), D60.1 (K), D61.1 (K), D62.1 (K), D63.1 (K), D64.1 (K), D65.1 (K), U1.8 (P04)
/ROW5: D66.1 (K), D67.1 (K), D68.1 (K), D69.1 (K), D70.1 (K), D71.1 (K), D72.1 (K), D73.1 (K), D74.1 (K), D75.1 (K), D76.1 (K), D77.1 (K), D78.1 (K), U1.9 (P05)
/ROW6: D79.1 (K), D80.1 (K), D81.1 (K), D82.1 (K), D83.1 (K), D84.1 (K), D85.1 (K), D86.1 (K), D87.1 (K), D88.1 (K), D89.1 (K), D90.1 (K), D91.1 (K), U1.10 (P06)
/ROW7: D92.1 (K), D93.1 (K), D94.1 (K), D95.1 (K), D96.1 (K), D97.1 (K), D98.1 (K), D99.1 (K), D100.1 (K), D101.1 (K), D102.1 (K), D103.1 (K), D104.1 (K), U1.11 (P07)
/USB_VBUS_5V: A1.8 (5V), F2.1
/VBAT_FUSED: F1.2, SWP1.1 (A)
/VBAT_RAW: F1.1, J1.1
/VBAT_SW: A1.16 (BAT+), C3.1, J4.6, SWP1.2 (B), U3.2, U3.8
unnamed: LED105.2 (A), R4.2
unnamed: LED106.2 (A), R5.2
unnamed: LED107.2 (A), R6.2
unnamed: LED108.2 (A), R7.2
unnamed: LED109.2 (A), R8.2
unnamed: R12.1, U5.4

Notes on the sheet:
ROW0
COL8
+5V_RGB
COL7
CAPS LOCK
COL1
NUM LOCK
BLE HOST 2
GND
COL2
COL10
COL5
COL9
ROW6
ROW1
BLE HOST 3
COL12
COL3
ROW2
ROW3
ROW4
COL6
BLE HOST 1
COL11
ROW5
COL0
COL4
ROW7

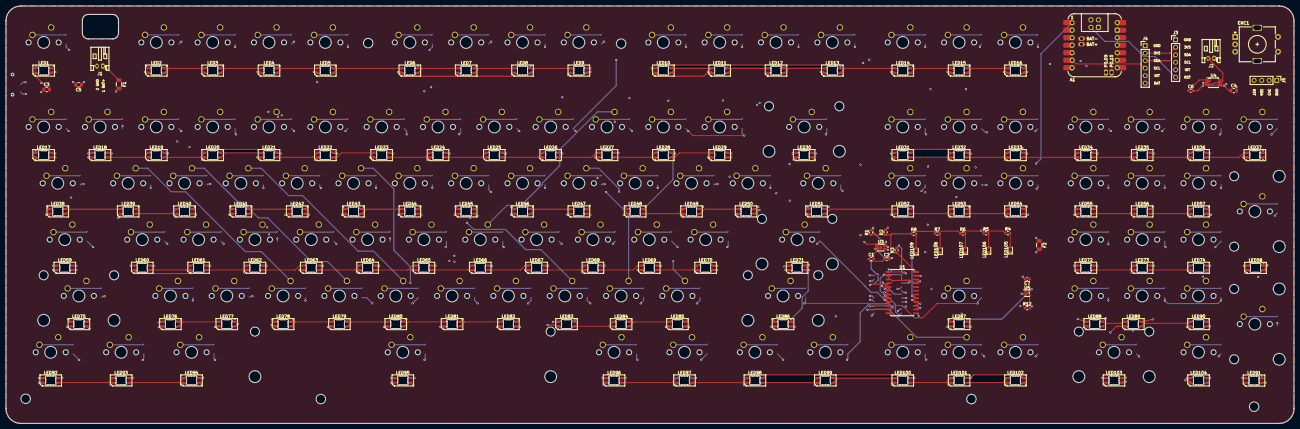
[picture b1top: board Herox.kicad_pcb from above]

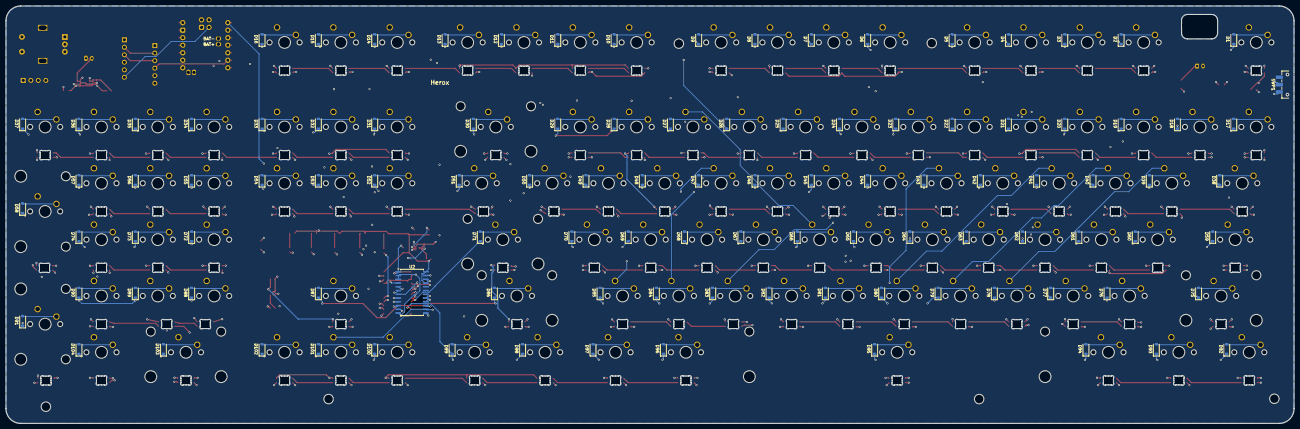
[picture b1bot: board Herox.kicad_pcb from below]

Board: 4 copper layers, 435.6 x 141.2 mm, 354 parts (106 on the bottom side), 260 nets.

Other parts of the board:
H2, H3, H5, H6, H7, H8: M3; MountingHole_3.2mm_M3

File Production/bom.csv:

Designator,Footprint,Quantity,Value,LCSC Part #
A1,Xiao_nRF52840_ACH,1,Seeeduino XIAO nRF52840,
C1,0603,1,100n U1,
C2,0603,1,100n U2,
C3,0805,1,10u BAT,
C4,0805,1,10u MCU,
C5,0805,1,47u RGB,
C6,0603,1,1u DRV REG,
C7,0603,1,100nF X7R,
"D1, D10, D100, D101, D102, D103, D104, D11, D12, D13, D14, D15, D16, D17, D18, D19, D2, D20, D21, D22, D23, D24, D25, D26, D27, D28, D29, D3, D30, D31, D32, D33, D34, D35, D36, D37, D38, D39, D4, D40, D41, D42, D43, D44, D45, D46, D47, D48, D49, D5, D50, D51, D52, D53, D54, D55, D56, D57, D58, D59, D6, D60, D61, D62, D63, D64, D65, D66, D67, D68, D69, D7, D70, D71, D72, D73, D74, D75, D76, D77, D78, D79, D8, D80, D81, D82, D83, D84, D85, D86, D87, D88, D89, D9, D90, D91, D92, D93, D94, D95, D96, D97, D98, D99",D_SOD-123,104,1N4148W,
ENC1,RotaryEncoder_Alps_EC11E-Switch_Vertical_H20mm,1,MEDIA ENCODER,
F1,1206,1,PTC 1.1A,
F2,1206,1,PTC 0.5A / USB RGB,
J1,JST_PH_S2B-PH-K_1x02_P2.00mm_Horizontal,1,PROTECTED Li-Po 3.7V,
J2,JST_PH_S2B-PH-K_1x02_P2.00mm_Horizontal,1,LRA ACTUATOR,
J3,PinHeader_1x06_P2.54mm_Vertical,1,LOW-POWER DISPLAY,
J4,PinHeader_1x06_P2.54mm_Vertical,1,AMBIENT SENSOR / EXPANSION,
J5,PinHeader_1x04_P2.54mm_Vertical,1,SWD DEBUG,
"LED1, LED10, LED100, LED101, LED102, LED103, LED104, LED11, LED12, LED13, LED14, LED15, LED16, LED17, LED18, LED19, LED2, LED20, LED21, LED22, LED23, LED24, LED25, LED26, LED27, LED28, LED29, LED3, LED30, LED31, LED32, LED33, LED34, LED35, LED36, LED37, LED38, LED39, LED4, LED40, LED41, LED42, LED43, LED44, LED45, LED46, LED47, LED48, LED49, LED5, LED50, LED51, LED52, LED53, LED54, LED55, LED56, LED57, LED58, LED59, LED6, LED60, LED61, LED62, LED63, LED64, LED65, LED66, LED67, LED68, LED69, LED7, LED70, LED71, LED72, LED73, LED74, LED75, LED76, LED77, LED78, LED79, LED8, LED80, LED81, LED82, LED83, LED84, LED85, LED86, LED87, LED88, LED89, LED9, LED90, LED91, LED92, LED93, LED94, LED95, LED96, LED97, LED98, LED99",LED_SK6812MINI-E_3.2x2.8mm_P1.5mm_ReverseMount,104,SK6812MINI-E,
"LED105, LED106",0603,2,XL-1608UGC-04 GREEN,
"LED107, LED108, LED109",0603,3,LTST-C193TBKT-5A BLUE,
R1,0603,1,4.7k SDA,
R12,0603,1,33R,
R2,0603,1,4.7k SCL,
R3,0603,1,10k INT,
"R4, R5, R6, R7, R8",0603,5,1k STATUS,
SW1,SW_MX_1.00u,1,Esc,
SW10,SW_MX_1.00u,1,F9,
SW100,SW_MX_1.00u,1,Left,
SW101,SW_MX_1.00u,1,Down,
SW102,SW_MX_1.00u,1,Right,
SW103,SW_MX_2.00u,1,0,
SW104,SW_MX_1.00u,1,.,
SW11,SW_MX_1.00u,1,F10,
SW12,SW_MX_1.00u,1,F11,
SW13,SW_MX_1.00u,1,F12,
SW14,SW_MX_1.00u,1,PrtSc,
SW15,SW_MX_1.00u,1,Scroll,
SW16,SW_MX_1.00u,1,Pause,
SW17,SW_MX_1.00u,1,`~,
SW18,SW_MX_1.00u,1,1!,
SW19,SW_MX_1.00u,1,2@,
SW2,SW_MX_1.00u,1,F1,
SW20,SW_MX_1.00u,1,3#,
SW21,SW_MX_1.00u,1,4$,
SW22,SW_MX_1.00u,1,5%,
SW23,SW_MX_1.00u,1,6^,
SW24,SW_MX_1.00u,1,7&,
SW25,SW_MX_1.00u,1,8*,
SW26,SW_MX_1.00u,1,9(,
SW27,SW_MX_1.00u,1,0),
SW28,SW_MX_1.00u,1,-_,
SW29,SW_MX_1.00u,1,=+,
SW3,SW_MX_1.00u,1,F2,
SW30,SW_MX_2.00u,1,Backspace,
SW31,SW_MX_1.00u,1,Insert,
SW32,SW_MX_1.00u,1,Home,
SW33,SW_MX_1.00u,1,PgUp,
SW34,SW_MX_1.00u,1,Num,
SW35,SW_MX_1.00u,1,/,
SW36,SW_MX_1.00u,1,*,
SW37,SW_MX_1.00u,1,-,
SW38,SW_MX_1.50u,1,Tab,
SW39,SW_MX_1.00u,1,Q,
SW4,SW_MX_1.00u,1,F3,
SW40,SW_MX_1.00u,1,W,
SW41,SW_MX_1.00u,1,E,
SW42,SW_MX_1.00u,1,R,
SW43,SW_MX_1.00u,1,T,
SW44,SW_MX_1.00u,1,Y,
SW45,SW_MX_1.00u,1,U,
SW46,SW_MX_1.00u,1,I,
SW47,SW_MX_1.00u,1,O,
SW48,SW_MX_1.00u,1,P,
SW49,SW_MX_1.00u,1,[{,
SW5,SW_MX_1.00u,1,F4,
SW50,SW_MX_1.00u,1,]},
SW51,SW_MX_1.50u,1,\|,
SW52,SW_MX_1.00u,1,Delete,
SW53,SW_MX_1.00u,1,End,
SW54,SW_MX_1.00u,1,PgDn,
SW55,SW_MX_1.00u,1,7,
SW56,SW_MX_1.00u,1,8,
SW57,SW_MX_1.00u,1,9,
SW58,SW_MX_2.00u_Vertical,1,+,
SW59,SW_MX_1.75u,1,Caps,
SW6,SW_MX_1.00u,1,F5,
SW60,SW_MX_1.00u,1,A,
SW61,SW_MX_1.00u,1,S,
SW62,SW_MX_1.00u,1,D,
SW63,SW_MX_1.00u,1,F,
SW64,SW_MX_1.00u,1,G,
SW65,SW_MX_1.00u,1,H,
SW66,SW_MX_1.00u,1,J,
SW67,SW_MX_1.00u,1,K,
SW68,SW_MX_1.00u,1,L,
SW69,SW_MX_1.00u,1,;:,
SW7,SW_MX_1.00u,1,F6,
SW70,SW_MX_1.00u,1,"'""",
SW71,SW_MX_2.25u,1,Enter,
SW72,SW_MX_1.00u,1,4,
SW73,SW_MX_1.00u,1,5,
SW74,SW_MX_1.00u,1,6,
SW75,SW_MX_2.25u,1,LShift,
SW76,SW_MX_1.00u,1,Z,
SW77,SW_MX_1.00u,1,X,
SW78,SW_MX_1.00u,1,C,
SW79,SW_MX_1.00u,1,V,
SW8,SW_MX_1.00u,1,F7,
SW80,SW_MX_1.00u,1,B,
SW81,SW_MX_1.00u,1,N,
SW82,SW_MX_1.00u,1,M,
SW83,SW_MX_1.00u,1,",<",
SW84,SW_MX_1.00u,1,.>,
SW85,SW_MX_1.00u,1,/?,
SW86,SW_MX_2.75u,1,RShift,
SW87,SW_MX_1.00u,1,Up,
SW88,SW_MX_1.00u,1,1,
SW89,SW_MX_1.00u,1,2,
SW9,SW_MX_1.00u,1,F8,
SW90,SW_MX_1.00u,1,3,
SW91,SW_MX_2.00u_Vertical,1,NEnter,
SW92,SW_MX_1.25u,1,LCtrl,
SW93,SW_MX_1.25u,1,LWin,
SW94,SW_MX_1.25u,1,LAlt,
SW95,SW_MX_6.25u,1,Space,
SW96,SW_MX_1.25u,1,RAlt,
SW97,SW_MX_1.25u,1,RWin,
SW98,SW_MX_1.25u,1,Menu,
SW99,SW_MX_1.25u,1,RCtrl,
SWP1,SW_SPDT_CK_JS102011SAQN,1,HARD POWER,
U1,SOIC-24W_7.5x15.4mm_P1.27mm,1,TCA9555DW / ROW DRIVE,
U2,SOIC-24W_7.5x15.4mm_P1.27mm,1,TCA9555DW / COLUMN SENSE,
U3,TDFN-8-1EP_2x2mm_P0.5mm_EP0.8x1.2mm,1,MAX17048G+T10 FUEL GAUGE,
U4,MSOP-10_3x3mm_P0.5mm,1,DRV2605L HAPTIC DRIVER,
U5,SOT-353_SC-70-5,1,"74LVC1G125GW,125",
